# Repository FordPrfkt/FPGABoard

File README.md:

# FPGABoard
A Xilinx Spartan 3A Development Board

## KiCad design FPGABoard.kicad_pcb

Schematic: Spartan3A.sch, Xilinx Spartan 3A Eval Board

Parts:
C1, C2, C3, C4, C5, C6, C7, C8, C9, C10, C11, C12, C13, C14, C29: 100nF; C_0603_HandSoldering
C17, C19, C21: 1µF; C_0805_HandSoldering
D1: Green; LED_0805
D14, D15: BAT54A; SOT-23
P1: JTAG_FPGA; vasch_strip_7x2
Q1: BSS123; SOT-23_Handsoldering
R1, R3: 4k7; R_0805_HandSoldering
R2, R22: 330R; R_0805_HandSoldering
R16: 36R; R_0805_HandSoldering
R21, R23, R24, R25: 15k; R_0805_HandSoldering
SW3: SW_Push; SW_SPST_B3S-1000
SW4: SW_DIP_x02; dip_2-300
U1: XC3S50A/VQ100; TQFP-100_14x14mm_Pitch0.5mm
U6: M25P20; SOIC-8_3.9x4.9mm_Pitch1.27mm
U7: XO53; Oscillator_XO53

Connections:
/Connections/BTN1: U1.97 (IP_0); also elsewhere on the board
/Connections/BTN2: U1.82 (IP_0/VREF_0); also elsewhere on the board
/Connections/GPIO01: U1.78 (IO_L01N_0); also elsewhere on the board
/Connections/GPIO02: U1.77 (IO_L01P_0/VREF_0); also elsewhere on the board
/Connections/GPIO03: U1.84 (IO_L02N_0/GCLK5); also elsewhere on the board
/Connections/GPIO04: U1.83 (IO_L02P_0/GCLK4); also elsewhere on the board
/Connections/GPIO05: U1.86 (IO_L03N_0/GCLK7); also elsewhere on the board
/Connections/GPIO06: U1.85 (IO_L03P_0/GCLK6); also elsewhere on the board
/Connections/GPIO07: U1.89 (IO_L04N_0/GCLK9); also elsewhere on the board
/Connections/GPIO08: U1.88 (IO_L04P_0/GCLK8); also elsewhere on the board
/Connections/GPIO09: U1.94 (IO_L05N_0); also elsewhere on the board
/Connections/GPIO010: U1.93 (IO_L05P_0); also elsewhere on the board
/Connections/GPIO11: U1.57 (IO_L01N_1); also elsewhere on the board
/Connections/GPIO011: U1.99 (IO_L06N_0/PUDC_B); also elsewhere on the board
/Connections/GPIO12: U1.56 (O_L01P_1); also elsewhere on the board
/Connections/GPIO012: U1.98 (IO_L06P_0/VREF_0); also elsewhere on the board
/Connections/GPIO13: U1.60 (IO_L02N_1/RHCLK1); also elsewhere on the board
/Connections/GPIO14: U1.59 (IO_L02P_1/RHCLK0); also elsewhere on the board
/Connections/GPIO15: U1.62 (IO_L03N_1/TRDY1/RHCLK3); also elsewhere on the board
/Connections/GPIO16: U1.61 (IO_L03P_1/RHCLK2); also elsewhere on the board
/Connections/GPIO17: U1.65 (IO_L04N_1/RHCLK7); also elsewhere on the board
/Connections/GPIO18: U1.64 (IO_L04P_1/IRDY1/RHCLK6); also elsewhere on the board
/Connections/GPIO19: U1.71 (IO_L05N_1); also elsewhere on the board
/Connections/GPIO21: U1.4 (IO_L01N_3); also elsewhere on the board
/Connections/GPIO22: U1.3 (IO_L01P_3); also elsewhere on the board
/Connections/GPIO23: U1.6 (IO_L02N_3); also elsewhere on the board
/Connections/GPIO24: U1.5 (IO_L02P_3); also elsewhere on the board
/Connections/GPIO25: U1.10 (IO_L03N_3/LHCLK1); also elsewhere on the board
/Connections/GPIO26: U1.9 (IO_L03P_3/LHCLK0); also elsewhere on the board
/Connections/GPIO27: U1.13 (IO_L04N_3/IRDY2/LHCLK3); also elsewhere on the board
/Connections/GPIO28: U1.12 (IO_L04P_3/LHCLK2); also elsewhere on the board
/Connections/GPIO29: U1.16 (IO_L05N_3/LHCLK7); also elsewhere on the board
/Connections/GPIO31: U1.34 (IO_L05N_2/D7); also elsewhere on the board
/Connections/GPIO32: U1.32 (IO_L05P_2); also elsewhere on the board
/Connections/GPIO33: U1.35 (IO_L06N_2/D6); also elsewhere on the board
/Connections/GPIO34: U1.33 (IO_L06P_2); also elsewhere on the board
/Connections/GPIO35: U1.37 (IO_L07N_2/D4); also elsewhere on the board
/Connections/GPIO36: U1.36 (IO_L07P_2/D5); also elsewhere on the board
/Connections/GPIO37: U1.41 (IO_L08N_2/GCLK15); also elsewhere on the board
/Connections/GPIO38: U1.40 (IO_L08P_2/GCLK14); also elsewhere on the board
/Connections/GPIO39: U1.44 (IO_L09N_2/GCLK1); also elsewhere on the board
/Connections/GPIO110: U1.70 (IO_L05P_1); also elsewhere on the board
/Connections/GPIO111: U1.72 (IO_L06N_1); also elsewhere on the board
/Connections/GPIO112: U1.73 (IO_L06P_1); also elsewhere on the board
/Connections/GPIO210: U1.15 (IO_L05P_3/TRDY2/LHCLK6); also elsewhere on the board
/Connections/GPIO211: U1.20 (IO_L06N_3); also elsewhere on the board
/Connections/GPIO212: U1.19 (IO_L06P_3); also elsewhere on the board
/Connections/GPIO310: U1.43 (IO_L09P_2/GCLK0); also elsewhere on the board
/Connections/LED1: U1.49 (IO_L10N_2/D3); also elsewhere on the board
/Connections/LED2: U1.50 (IO_L11P_2/D2); also elsewhere on the board
/Connections/LED3: U1.52 (IO_L12P_2/D1); also elsewhere on the board
/Microcontroller/CS_C: U1.28 (IO_L03P_2/RDWR_B); also elsewhere on the board
/Microcontroller/CS_FLASH: U1.27 (IO_L02N_2/CSO_B), U6.1 (~CS); also elsewhere on the board
/Microcontroller/CS_FPGA: U1.39 (IP_2/VREF_2); also elsewhere on the board
/Microcontroller/DONE: Q1.1 (G), U1.54 (DONE); also elsewhere on the board
/Microcontroller/INIT_B: R3.1, U1.48 (IO_L10P_2/INIT_B); also elsewhere on the board
/Microcontroller/MISO_C: U1.51 (IO_L11N_2/D0/DIN/MISO), U6.2 (MISO); also elsewhere on the board
/Microcontroller/MOSI_C: D14.1 (K), R24.2; also elsewhere on the board
/Microcontroller/PROG_B: R1.1, SW3.1, U1.100 (PROG_B); also elsewhere on the board
/Microcontroller/SCK_C: D15.2 (K), R25.2; also elsewhere on the board
/Spartan3A/M1: SW4.4, U1.23 (IO_L01P_2/M1)
/Spartan3A/M2: SW4.3, U1.24 (IO_L02P_2/M2)
/Spartan3A/MOSI: D14.3 (A), R2.1, U6.5 (MOSI)
/Spartan3A/MOSI_F: D14.2 (K), R21.2, U1.46 (IO_2/MOSI/CSI_B)
/Spartan3A/SCK: D15.3 (A), R22.1, U6.6 (SCK)
/Spartan3A/SCK_F: D15.1 (K), R23.2, U1.53 (IO_L12N_2/CCLK)
GND: C1.2, C2.2, C3.2, C4.2, C5.2, C6.2, C7.2, C8.2, C9.2, C10.2, C11.2, C12.2, C13.2, C14.2, C17.2, C19.2, C21.2, C29.2, P1.1, P1.3, P1.5, P1.7, P1.9, P1.11, P1.13, Q1.2 (S), R21.1, R23.1, R24.1, R25.1, SW3.2, SW4.1, SW4.2, U1.8 (GND), U1.14 (GND), U1.18 (GND), U1.42 (GND), U1.47 (GND), U1.58 (GND), U1.63 (GND), U1.69 (GND), U1.74 (GND), U1.80 (GND), U1.87 (GND), U1.91 (GND), U1.95 (GND), U6.4 (GND), U7.2 (GND); also elsewhere on the board
unnamed: D1.1 (K), Q1.3 (D)
unnamed: D1.2 (A), R16.1
unnamed: P1.4, U1.1 (TMS)
unnamed: P1.6, U1.76 (TCK)
unnamed: P1.8, U1.75 (TDO)
unnamed: P1.10, U1.2 (TDI)
unnamed: U1.90 (IO_0/GCLK11), U7.3 (Clock)
VCC: C1.1, C2.1, C3.1, C4.1, C5.1, C6.1, C7.1, C17.1, C29.1, R2.2, R16.2, R22.2, U1.11 (VCCO3), U1.26 (VCCO2), U1.45 (VCCO2), U1.67 (VCCO1), U1.79 (VCCO0), U1.96 (VCCO0), U6.3 (~WP), U6.7 (~HOLD), U6.8 (Vcc), U7.1 (Enable), U7.4 (VCC); also elsewhere on the board
VCC_AUX: C8.1, C9.1, C10.1, C19.1, P1.2, R1.2, R3.2, U1.22 (VCCAUX), U1.55 (VCCAUX), U1.92 (VCCAUX); also elsewhere on the board
VCC_INT: C11.1, C12.1, C13.1, C14.1, C21.1, U1.17 (VCCINT), U1.38 (VCCINT), U1.66 (VCCINT), U1.81 (VCCINT); also elsewhere on the board

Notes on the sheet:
SPI Configuration Memory

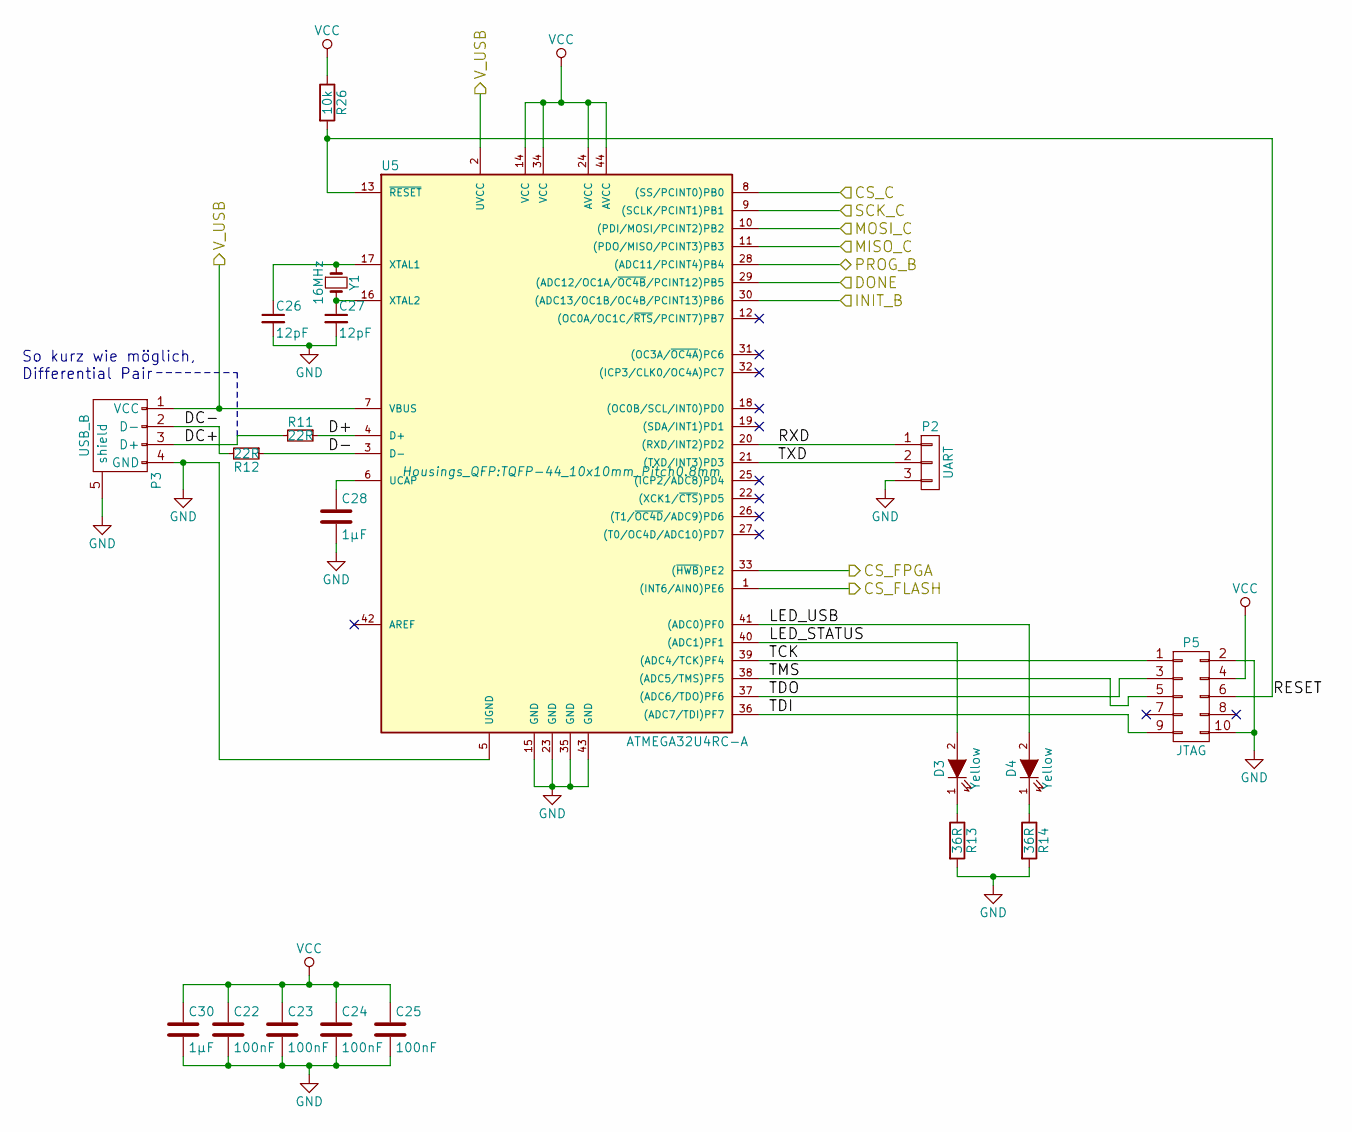
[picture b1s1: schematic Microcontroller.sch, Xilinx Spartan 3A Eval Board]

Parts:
C22, C23, C24, C25: 100nF; C_0603_HandSoldering
C26, C27: 12pF; C_0603_HandSoldering
C28, C30: 1µF; C_0805_HandSoldering
D3, D4: Yellow; LED_0805
P2: UART; Pin_Header_Straight_1x03_Pitch2.54mm
P3: USB_B; conn_usb_B_mini_smd
P5: JTAG; vasch_strip_5x2
R11, R12: 22R; R_0805_HandSoldering
R13, R14: 36R; R_0805_HandSoldering
R26: 10k; R_0805_HandSoldering
U5: ATMEGA32U4RC-A; TQFP-44_10x10mm_Pitch0.8mm
Y1: 16MHz; hc-49_smd

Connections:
/Microcontroller/CS_C: U5.8 ((SS/PCINT0)PB0); also elsewhere on the board
/Microcontroller/CS_FLASH: U5.1 ((INT6/AIN0)PE6); also elsewhere on the board
/Microcontroller/CS_FPGA: U5.33 ((~HWB~)PE2); also elsewhere on the board
/Microcontroller/D+: R11.1, U5.4 (D+)
/Microcontroller/D-: R12.1, U5.3 (D-)
/Microcontroller/DC+: P3.3 (D+), R11.2
/Microcontroller/DC-: P3.2 (D-), R12.2
/Microcontroller/DONE: U5.29 ((ADC12/OC1A/~OC4B~/PCINT12)PB5); also elsewhere on the board
/Microcontroller/INIT_B: U5.30 ((ADC13/OC1B/OC4B/PCINT13)PB6); also elsewhere on the board
/Microcontroller/LED_STATUS: D3.2 (A), U5.40 ((ADC1)PF1)
/Microcontroller/LED_USB: D4.2 (A), U5.41 ((ADC0)PF0)
/Microcontroller/MISO_C: U5.11 ((PDO/MISO/PCINT3)PB3); also elsewhere on the board
/Microcontroller/MOSI_C: U5.10 ((PDI/MOSI/PCINT2)PB2); also elsewhere on the board
/Microcontroller/PROG_B: U5.28 ((ADC11/PCINT4)PB4); also elsewhere on the board
/Microcontroller/RESET: P5.6, R26.2, U5.13 (~RESET~)
/Microcontroller/RXD: P2.1, U5.20 ((RXD/INT2)PD2)
/Microcontroller/SCK_C: U5.9 ((SCLK/PCINT1)PB1); also elsewhere on the board
/Microcontroller/TCK: P5.1, U5.39 ((ADC4/TCK)PF4)
/Microcontroller/TDI: P5.9, U5.36 ((ADC7/TDI)PF7)
/Microcontroller/TDO: P5.3, U5.37 ((ADC6/TDO)PF6)
/Microcontroller/TMS: P5.5, U5.38 ((ADC5/TMS)PF5)
/Microcontroller/TXD: P2.2, U5.21 ((TXD/INT3)PD3)
/Microcontroller/V_USB: P3.1 (VCC), U5.2 (UVCC), U5.7 (VBUS); also elsewhere on the board
GND: C22.2, C23.2, C24.2, C25.2, C26.2, C27.2, C28.2, C30.2, P2.3, P3.4 (GND), P3.5 (shield), P5.2, P5.10, R13.2, R14.2, U5.5 (UGND), U5.15 (GND), U5.23 (GND), U5.35 (GND), U5.43 (GND); also elsewhere on the board
unnamed: C26.1, U5.17 (XTAL1), Y1.1
unnamed: C27.1, U5.16 (XTAL2), Y1.2
unnamed: C28.1, U5.6 (UCAP)
unnamed: D3.1 (K), R13.1
unnamed: D4.1 (K), R14.1
VCC: C22.1, C23.1, C24.1, C25.1, C30.1, P5.4, R26.1, U5.14 (VCC), U5.24 (AVCC), U5.34 (VCC), U5.44 (AVCC); also elsewhere on the board

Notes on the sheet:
So kurz wie möglich, Differential Pair

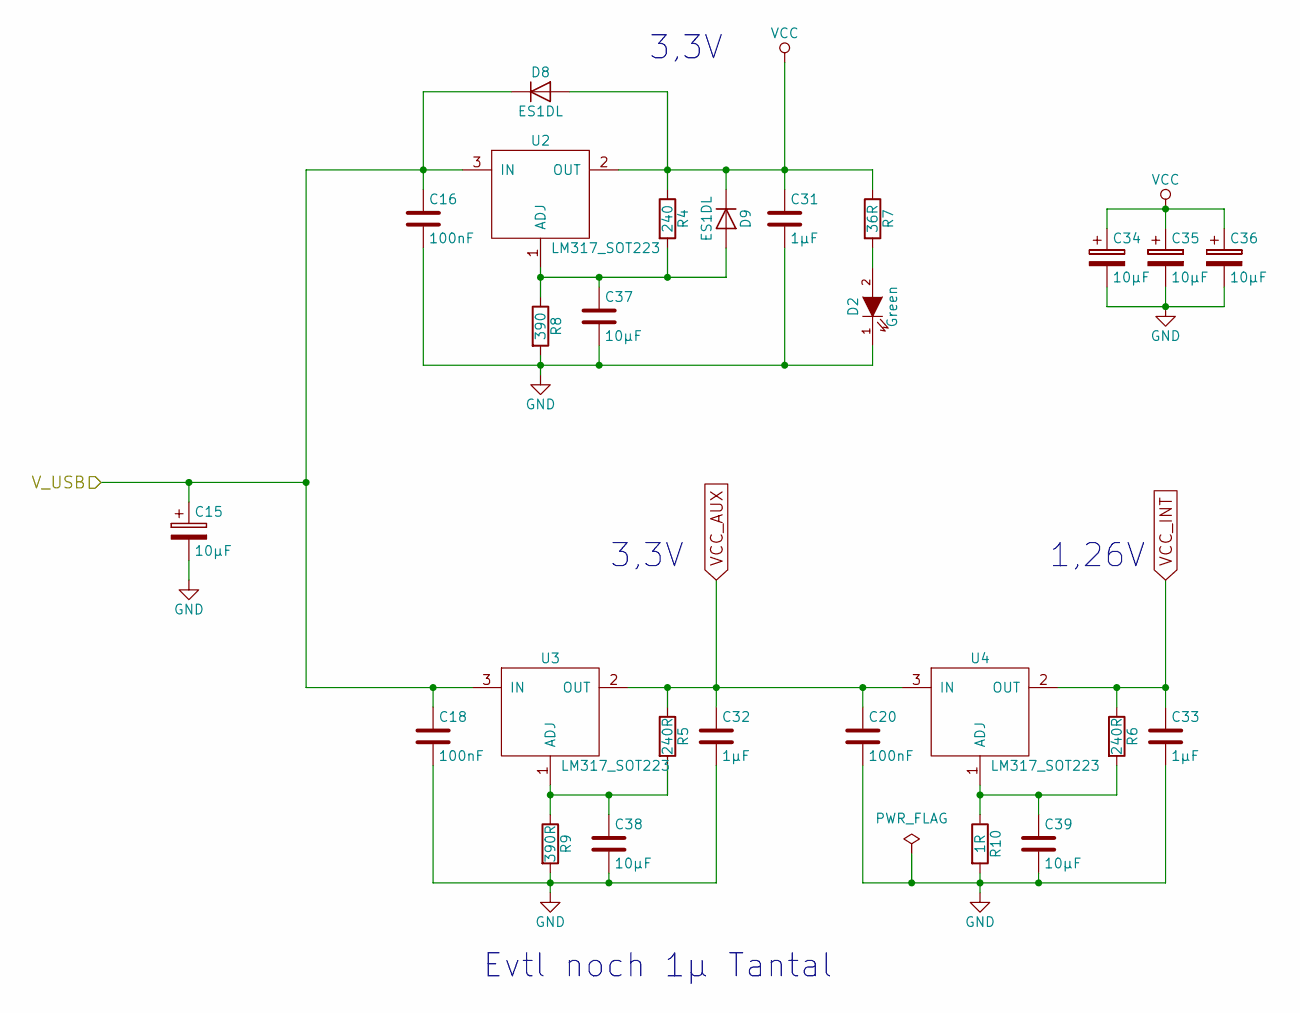
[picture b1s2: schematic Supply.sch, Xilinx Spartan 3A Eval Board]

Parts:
C15, C34, C35, C36: 10µF; c_elec_4x5.8
C16, C18, C20: 100nF; C_0805_HandSoldering
C31, C32, C33: 1µF; C_0805_HandSoldering
C37, C38, C39: 10µF; C_0805_HandSoldering
D2: Green; LED_0805
D8, D9: ES1DL; sod323
R4: 240; R_0805_HandSoldering
R5, R6: 240R; R_0805_HandSoldering
R7: 36R; R_0805_HandSoldering
R8: 390; R_0805_HandSoldering
R9: 390R; R_0805_HandSoldering
R10: 1R; R_0805_HandSoldering
U2, U3, U4: LM317_SOT223; SOT-223

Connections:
/Microcontroller/V_USB: C15.1, C16.1, C18.1, D8.1 (K), U2.3 (IN), U3.3 (IN); also elsewhere on the board
GND: C15.2, C16.2, C18.2, C20.2, C31.2, C32.2, C33.2, C34.2, C35.2, C36.2, C37.2, C38.2, C39.2, D2.1 (K), R8.2, R9.2, R10.2; also elsewhere on the board
unnamed: C37.1, D9.2 (A), R4.2, R8.1, U2.1 (ADJ)
unnamed: C38.1, R5.2, R9.1, U3.1 (ADJ)
unnamed: C39.1, R6.2, R10.1, U4.1 (ADJ)
unnamed: D2.2 (A), R7.2
VCC: C31.1, C34.1, C35.1, C36.1, D8.2 (A), D9.1 (K), R4.1, R7.1, U2.2 (OUT); also elsewhere on the board
VCC_AUX: C20.1, C32.1, R5.1, U3.2 (OUT), U4.3 (IN); also elsewhere on the board
VCC_INT: C33.1, R6.1, U4.2 (OUT); also elsewhere on the board

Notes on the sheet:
3,3V
1,26V
Evtl noch 1µ Tantal

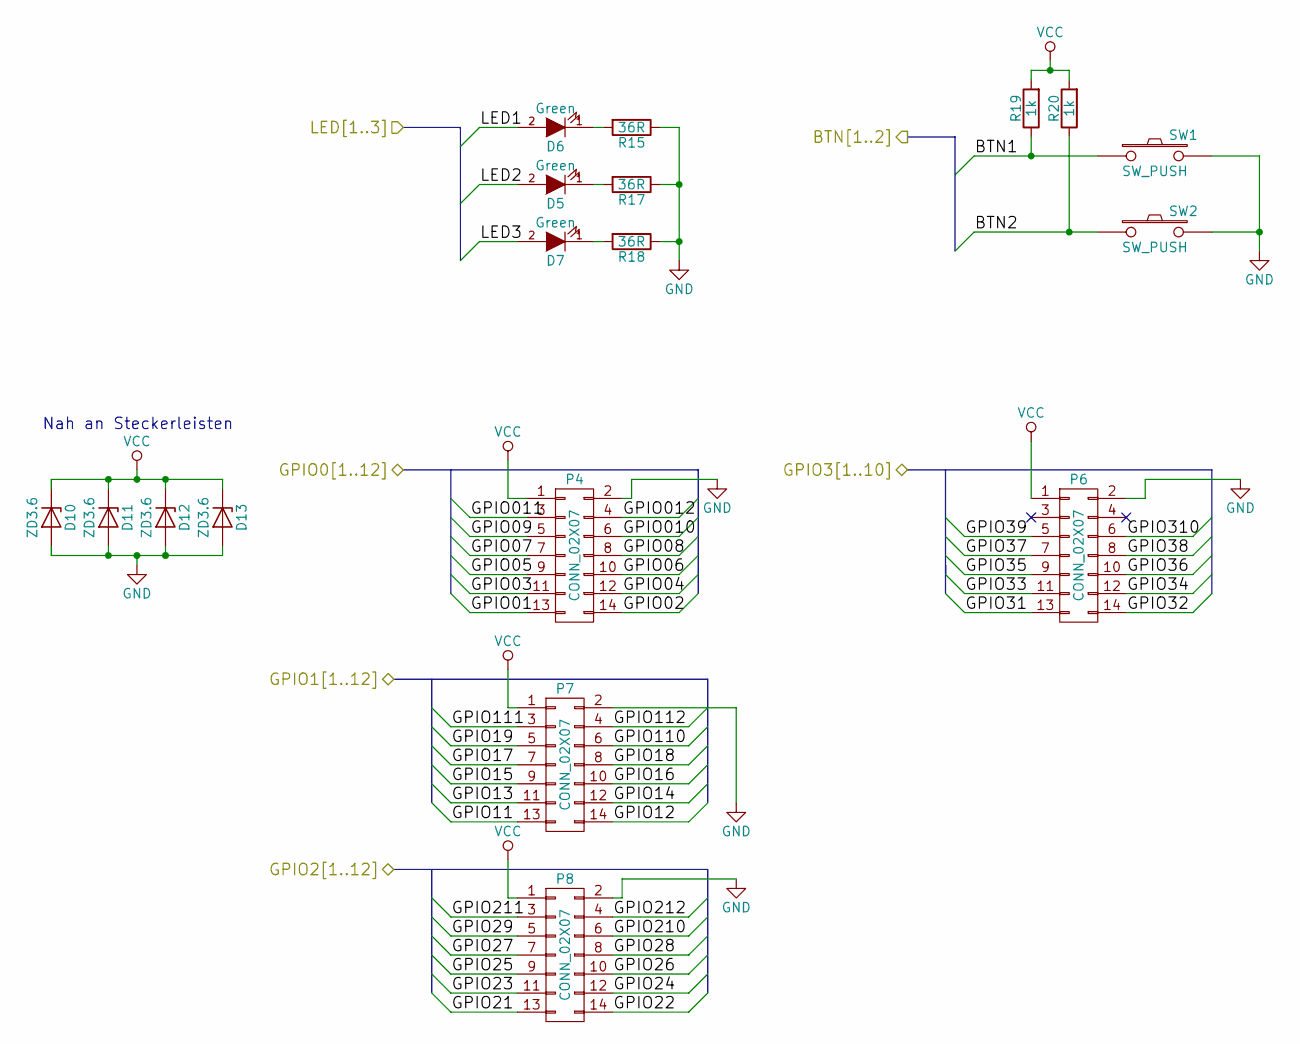
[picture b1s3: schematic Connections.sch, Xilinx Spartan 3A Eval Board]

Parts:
D5, D6, D7: Green; LED_0805
D10, D11, D12, D13: ZD3.6; D_SOT-23_ANK
P4, P6, P7, P8: CONN_02X07; vasch_strip_7x2_90
R15, R17, R18: 36R; R_0805_HandSoldering
R19, R20: 1k; R_0805_HandSoldering
SW1, SW2: SW_PUSH; SW_SPST_B3S-1000

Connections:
/Connections/BTN1: R19.1, SW1.1; also elsewhere on the board
/Connections/BTN2: R20.1, SW2.1; also elsewhere on the board
/Connections/GPIO01: P4.13; also elsewhere on the board
/Connections/GPIO02: P4.14; also elsewhere on the board
/Connections/GPIO03: P4.11; also elsewhere on the board
/Connections/GPIO04: P4.12; also elsewhere on the board
/Connections/GPIO05: P4.9; also elsewhere on the board
/Connections/GPIO06: P4.10; also elsewhere on the board
/Connections/GPIO07: P4.7; also elsewhere on the board
/Connections/GPIO08: P4.8; also elsewhere on the board
/Connections/GPIO09: P4.5; also elsewhere on the board
/Connections/GPIO010: P4.6; also elsewhere on the board
/Connections/GPIO11: P7.13; also elsewhere on the board
/Connections/GPIO011: P4.3; also elsewhere on the board
/Connections/GPIO12: P7.14; also elsewhere on the board
/Connections/GPIO012: P4.4; also elsewhere on the board
/Connections/GPIO13: P7.11; also elsewhere on the board
/Connections/GPIO14: P7.12; also elsewhere on the board
/Connections/GPIO15: P7.9; also elsewhere on the board
/Connections/GPIO16: P7.10; also elsewhere on the board
/Connections/GPIO17: P7.7; also elsewhere on the board
/Connections/GPIO18: P7.8; also elsewhere on the board
/Connections/GPIO19: P7.5; also elsewhere on the board
/Connections/GPIO21: P8.13; also elsewhere on the board
/Connections/GPIO22: P8.14; also elsewhere on the board
/Connections/GPIO23: P8.11; also elsewhere on the board
/Connections/GPIO24: P8.12; also elsewhere on the board
/Connections/GPIO25: P8.9; also elsewhere on the board
/Connections/GPIO26: P8.10; also elsewhere on the board
/Connections/GPIO27: P8.7; also elsewhere on the board
/Connections/GPIO28: P8.8; also elsewhere on the board
/Connections/GPIO29: P8.5; also elsewhere on the board
/Connections/GPIO31: P6.13; also elsewhere on the board
/Connections/GPIO32: P6.14; also elsewhere on the board
/Connections/GPIO33: P6.11; also elsewhere on the board
/Connections/GPIO34: P6.12; also elsewhere on the board
/Connections/GPIO35: P6.9; also elsewhere on the board
/Connections/GPIO36: P6.10; also elsewhere on the board
/Connections/GPIO37: P6.7; also elsewhere on the board
/Connections/GPIO38: P6.8; also elsewhere on the board
/Connections/GPIO39: P6.5; also elsewhere on the board
/Connections/GPIO110: P7.6; also elsewhere on the board
/Connections/GPIO111: P7.3; also elsewhere on the board
/Connections/GPIO112: P7.4; also elsewhere on the board
/Connections/GPIO210: P8.6; also elsewhere on the board
/Connections/GPIO211: P8.3; also elsewhere on the board
/Connections/GPIO212: P8.4; also elsewhere on the board
/Connections/GPIO310: P6.6; also elsewhere on the board
/Connections/LED1: D6.2 (A); also elsewhere on the board
/Connections/LED2: D5.2 (A); also elsewhere on the board
/Connections/LED3: D7.2 (A); also elsewhere on the board
GND: D10.2 (A), D11.2 (A), D12.2 (A), D13.2 (A), P4.2, P6.2, P7.2, P8.2, R15.1, R17.1, R18.1, SW1.2, SW2.2; also elsewhere on the board
unnamed: D5.1 (K), R17.2
unnamed: D6.1 (K), R15.2
unnamed: D7.1 (K), R18.2
VCC: D10.1 (K), D11.1 (K), D12.1 (K), D13.1 (K), P4.1, P6.1, P7.1, P8.1, R19.2, R20.2; also elsewhere on the board

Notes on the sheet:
Nah an Steckerleisten

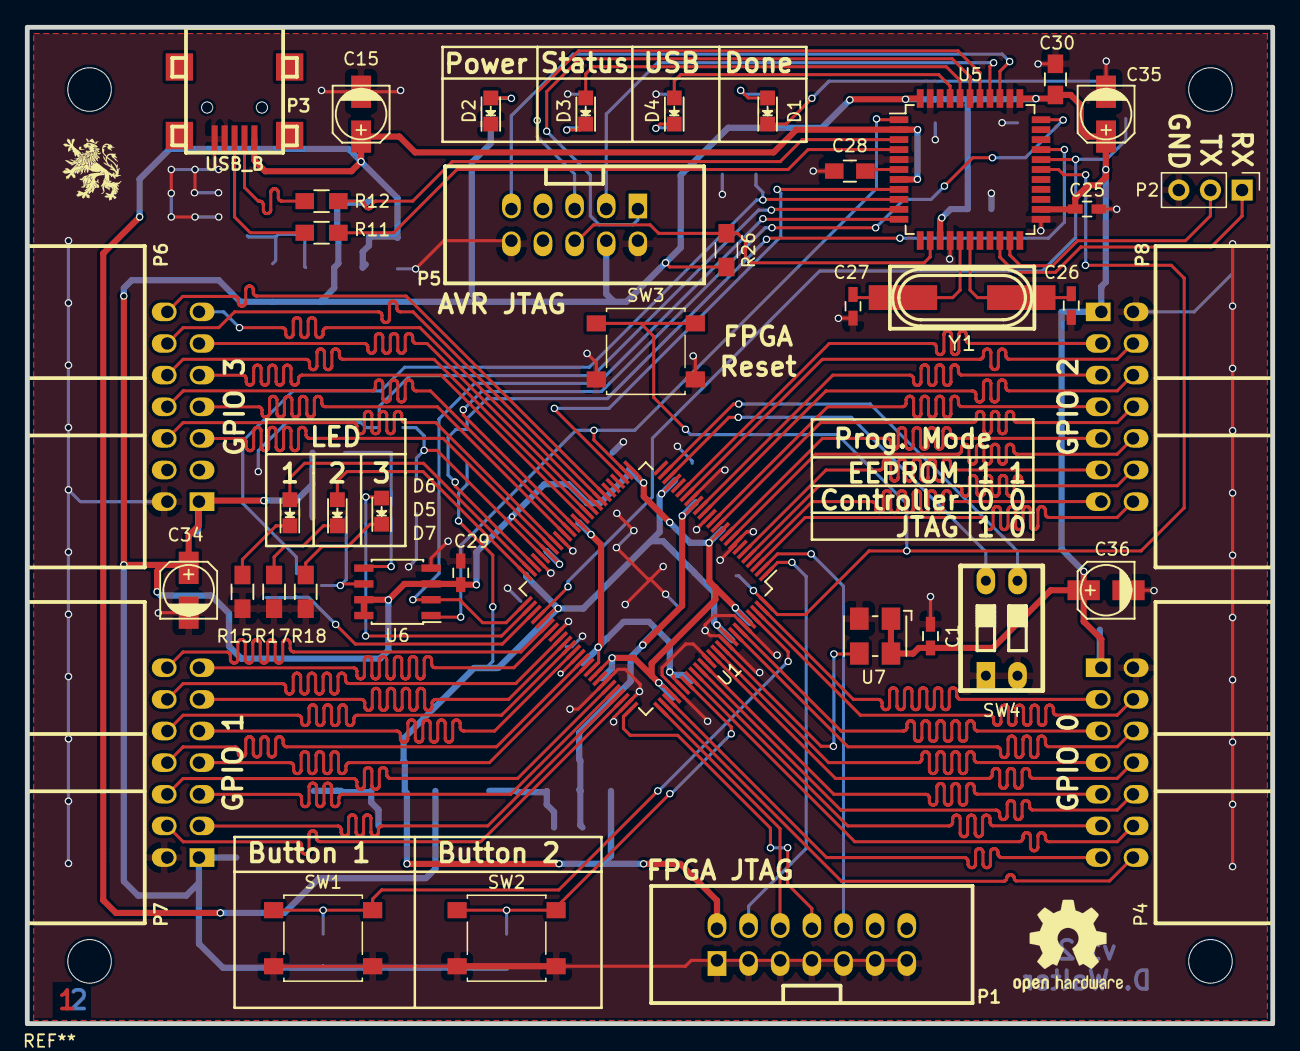
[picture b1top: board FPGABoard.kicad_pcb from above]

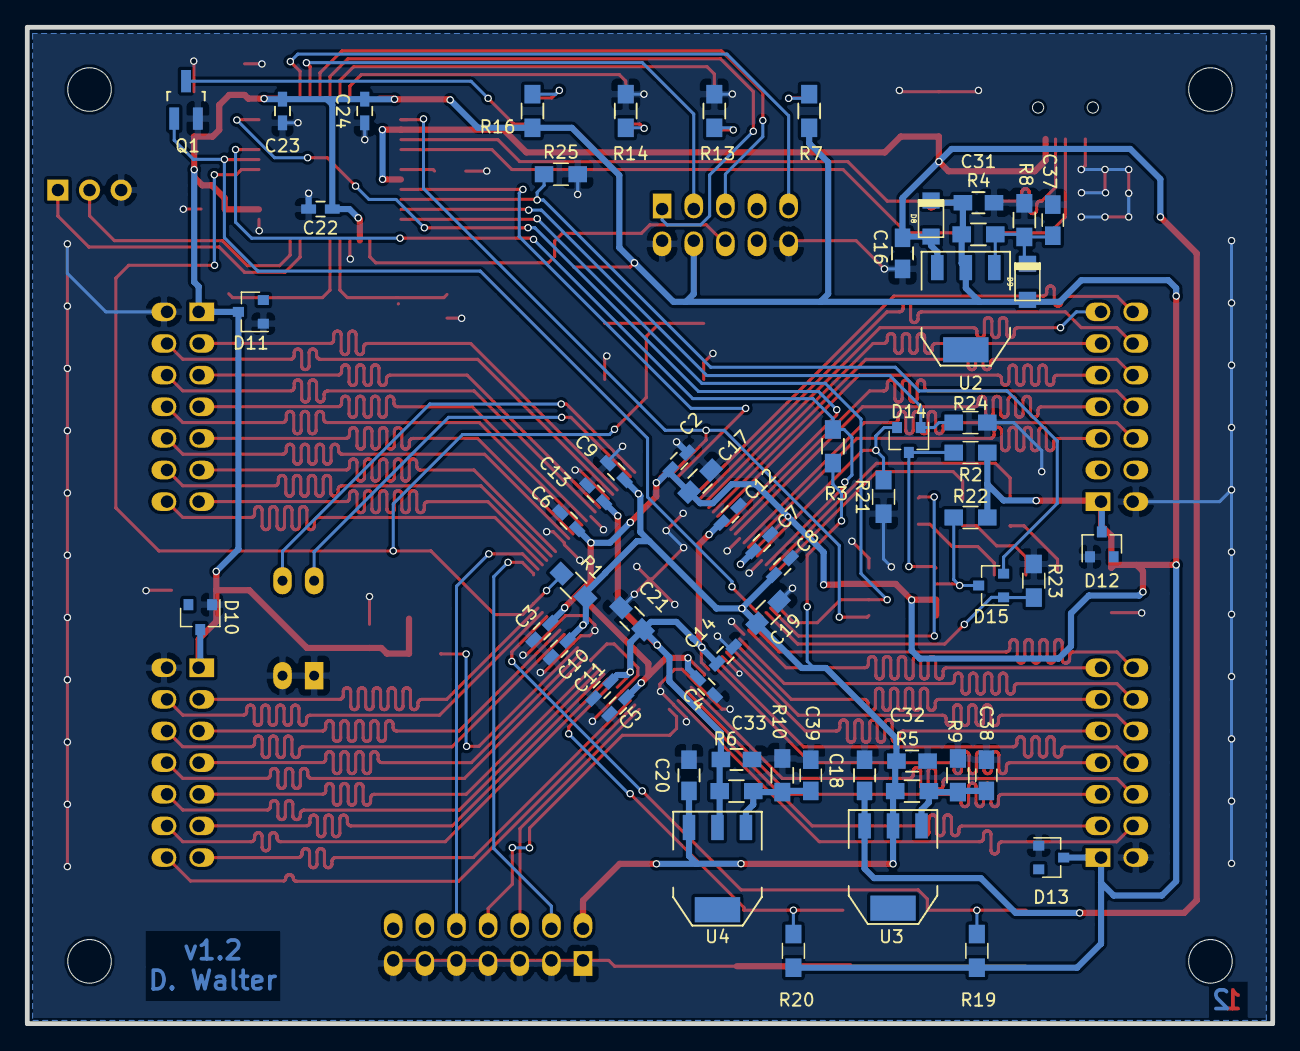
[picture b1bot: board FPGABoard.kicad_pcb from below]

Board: 2 copper layers, 100.0 x 80.0 mm, 101 parts (60 on the bottom side), 103 nets.

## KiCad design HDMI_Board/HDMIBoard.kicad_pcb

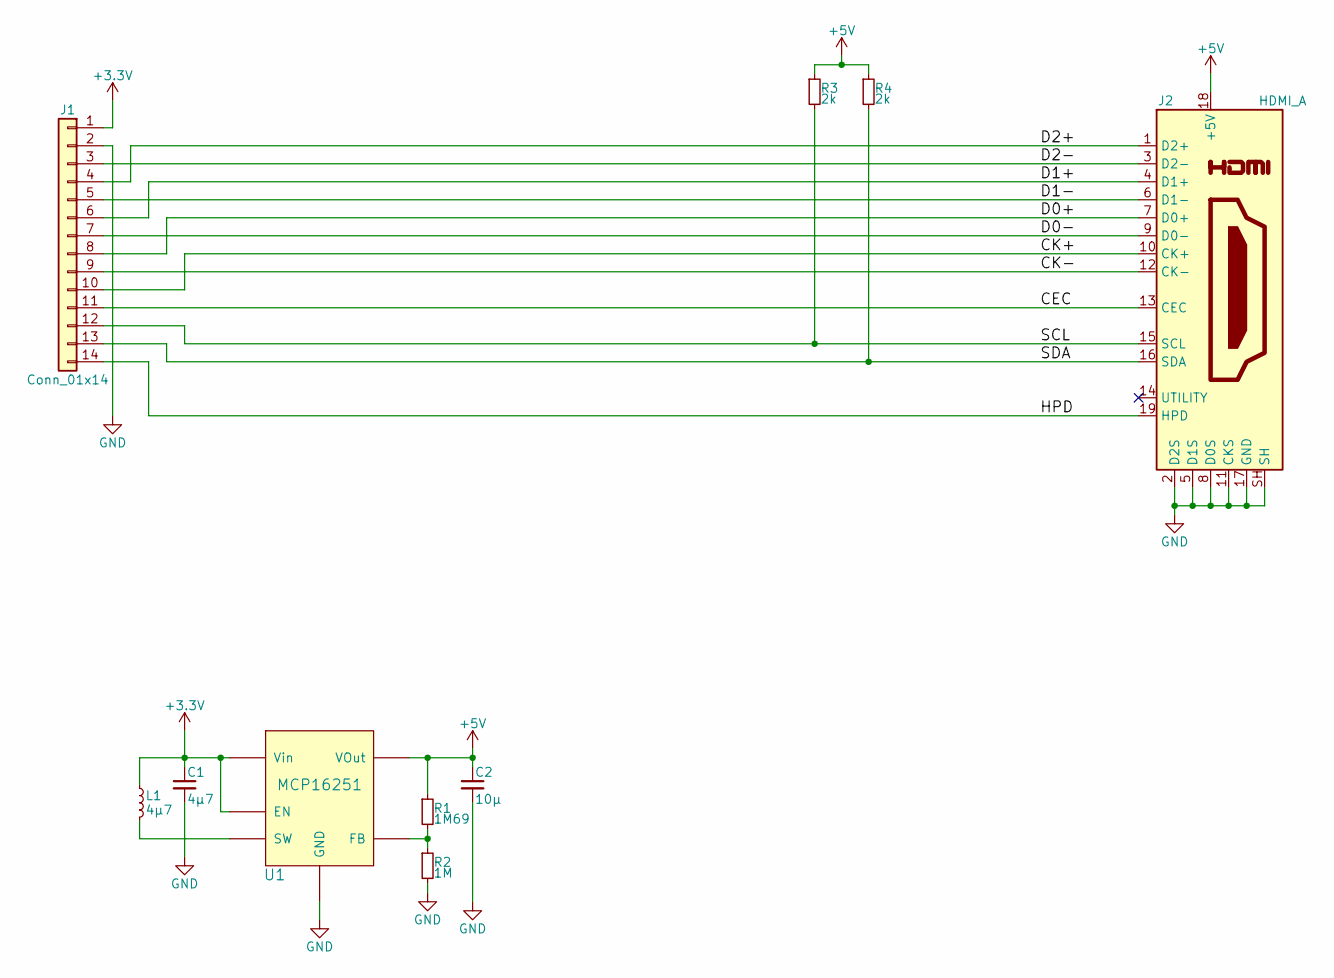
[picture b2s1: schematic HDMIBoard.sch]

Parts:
C1: 4µ7; C_0805
C2: 10µ; C_0805
J1: Conn_01x14; Socket_Strip_Angled_2x07_Pitch2.54mm
J2: HDMI_A; HDMI_A_SMD
L1: 4µ7; L_0805
R1: 1M69; R_0805
R2: 1M; R_0805
R3, R4: 2k; R_0805
U1: MCP16251; TSOP-6_1.65x3.05mm_Pitch0.95mm

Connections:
+3V3: C1.1, J1.1, L1.1, U1.3 (EN), U1.6 (Vin)
+5V: C2.1, J2.18 (+5V), R1.1, R3.1, R4.1, U1.5 (VOut)
/CEC: J1.11, J2.13 (CEC)
/CK+: J1.10, J2.10 (CK+)
/CK-: J1.9, J2.12 (CK-)
/D0+: J1.8, J2.7 (D0+)
/D0-: J1.7, J2.9 (D0-)
/D1+: J1.6, J2.4 (D1+)
/D1-: J1.5, J2.6 (D1-)
/D2+: J1.4, J2.1 (D2+)
/D2-: J1.3, J2.3 (D2-)
/HPD: J1.14, J2.19 (HPD)
/SCL: J1.12, J2.15 (SCL), R3.2
/SDA: J1.13, J2.16 (SDA), R4.2
GND: C1.2, C2.2, J1.2, J2.2 (D2S), J2.5 (D1S), J2.8 (D0S), J2.11 (CKS), J2.17 (GND), J2.SH, R2.2, U1.2 (GND)
unnamed: L1.2, U1.1 (SW)
unnamed: R1.2, R2.1, U1.4 (FB)

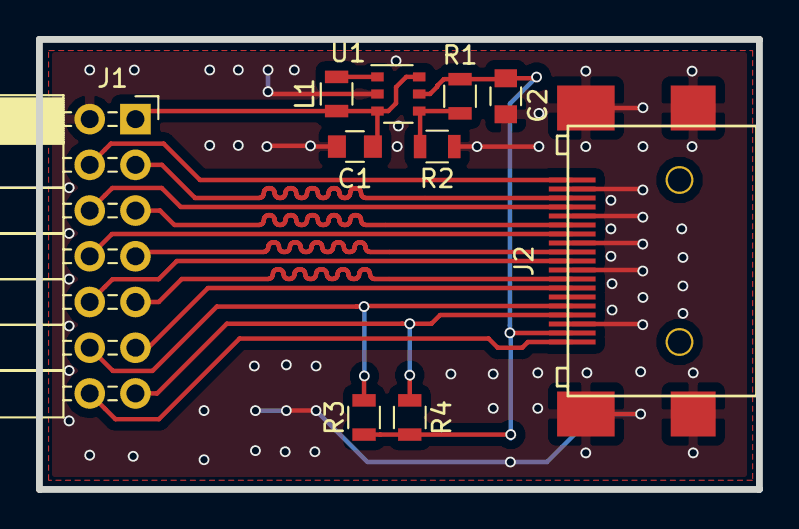
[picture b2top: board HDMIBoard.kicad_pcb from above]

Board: 2 copper layers, 40.0 x 25.0 mm, 10 parts (0 on the bottom side), 17 nets.

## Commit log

2016-07-18 Added README
2016-07-18 Added LICENSE
2016-07-19 Layouting
2016-07-23 Layout
2016-08-14 Additional Caps at VCC, Layout
2016-08-27 Work in Progress
2016-09-18 Small update
2016-09-19 Added Schematic PDF & Pictures
2016-10-08 All Resistors 0805, New Buttons
2017-03-03 Ready for Production
2017-03-04 Changed SPI Connection to support Multi-Master
2017-03-08 Added Resistor in Reset Line
2017-03-13 Release for Manufacture
2018-12-09 Added HDMI Interface
    Added a HDMI interface Board
2018-12-09 Updated KiCad
    After update to Kicad 5
2018-12-09 Added RAM Board
